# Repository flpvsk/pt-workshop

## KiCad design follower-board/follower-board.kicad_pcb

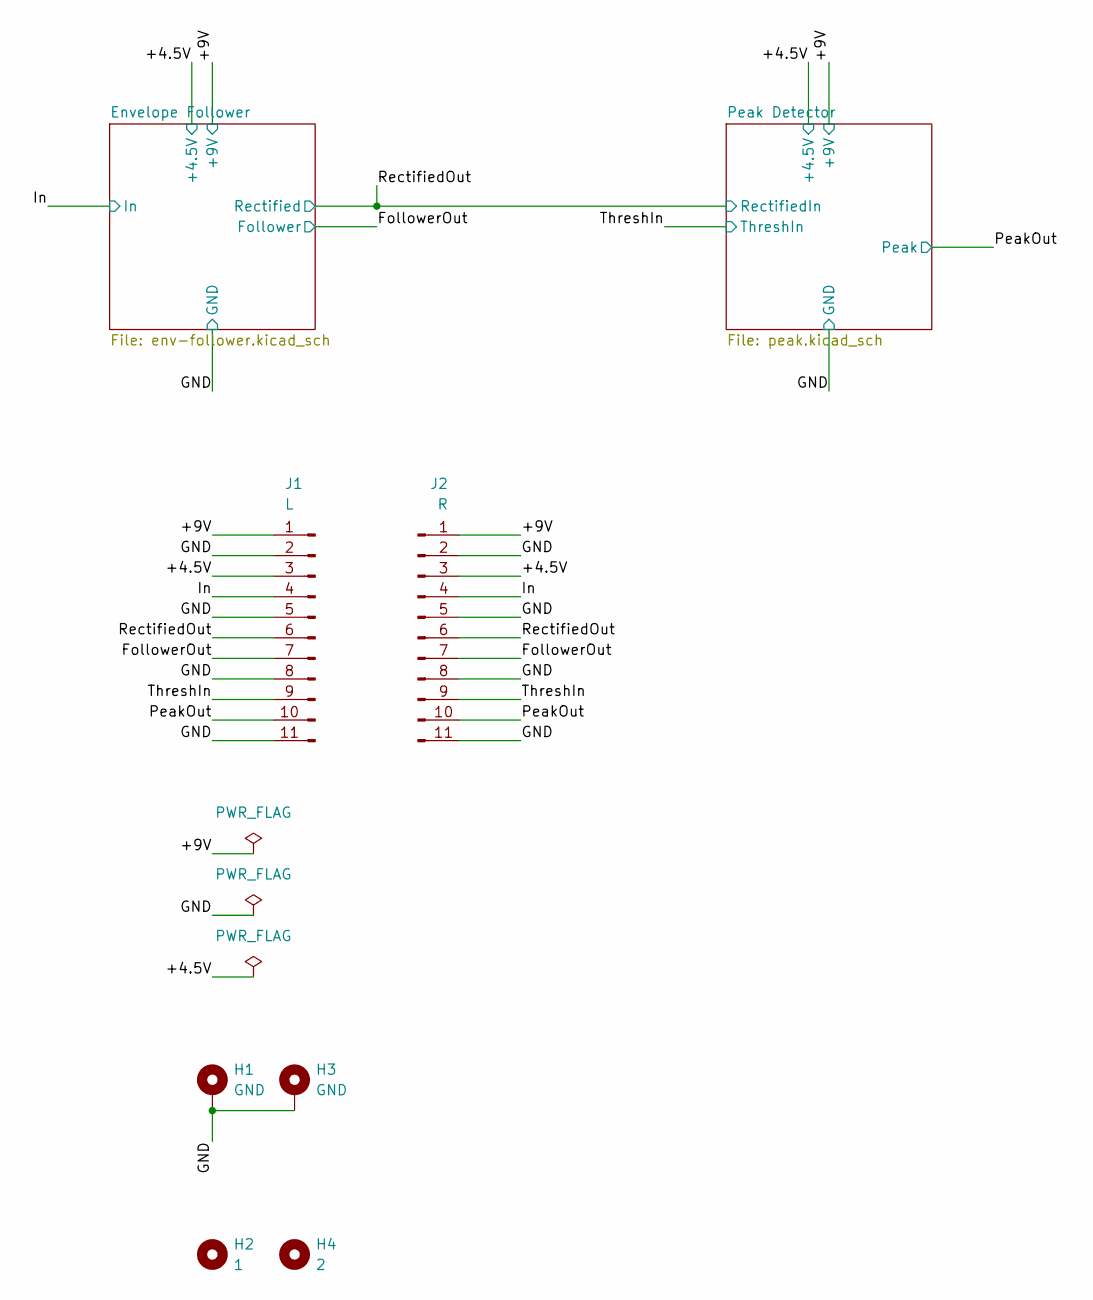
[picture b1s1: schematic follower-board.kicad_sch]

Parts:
H1, H3: GND; MountingHole_3.2mm_M3_ISO14580_Pad
H2: 1; MountingHole_3.2mm_M3
H4: 2; MountingHole_3.2mm_M3
J1: L; PinHeader_1x11_P2.54mm_Vertical
J2: R; PinHeader_1x11_P2.54mm_Vertical

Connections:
/+4.5V: J1.3, J2.3; also elsewhere on the board
/+9V: J1.1, J2.1; also elsewhere on the board
/FollowerOut: J1.7, J2.7; also elsewhere on the board
/GND: H1.1, H3.1, J1.2, J1.5, J1.8, J1.11, J2.2, J2.5, J2.8, J2.11; also elsewhere on the board
/In: J1.4, J2.4; also elsewhere on the board
/PeakOut: J1.10, J2.10; also elsewhere on the board
/RectifiedOut: J1.6, J2.6; also elsewhere on the board
/ThreshIn: J1.9, J2.9; also elsewhere on the board

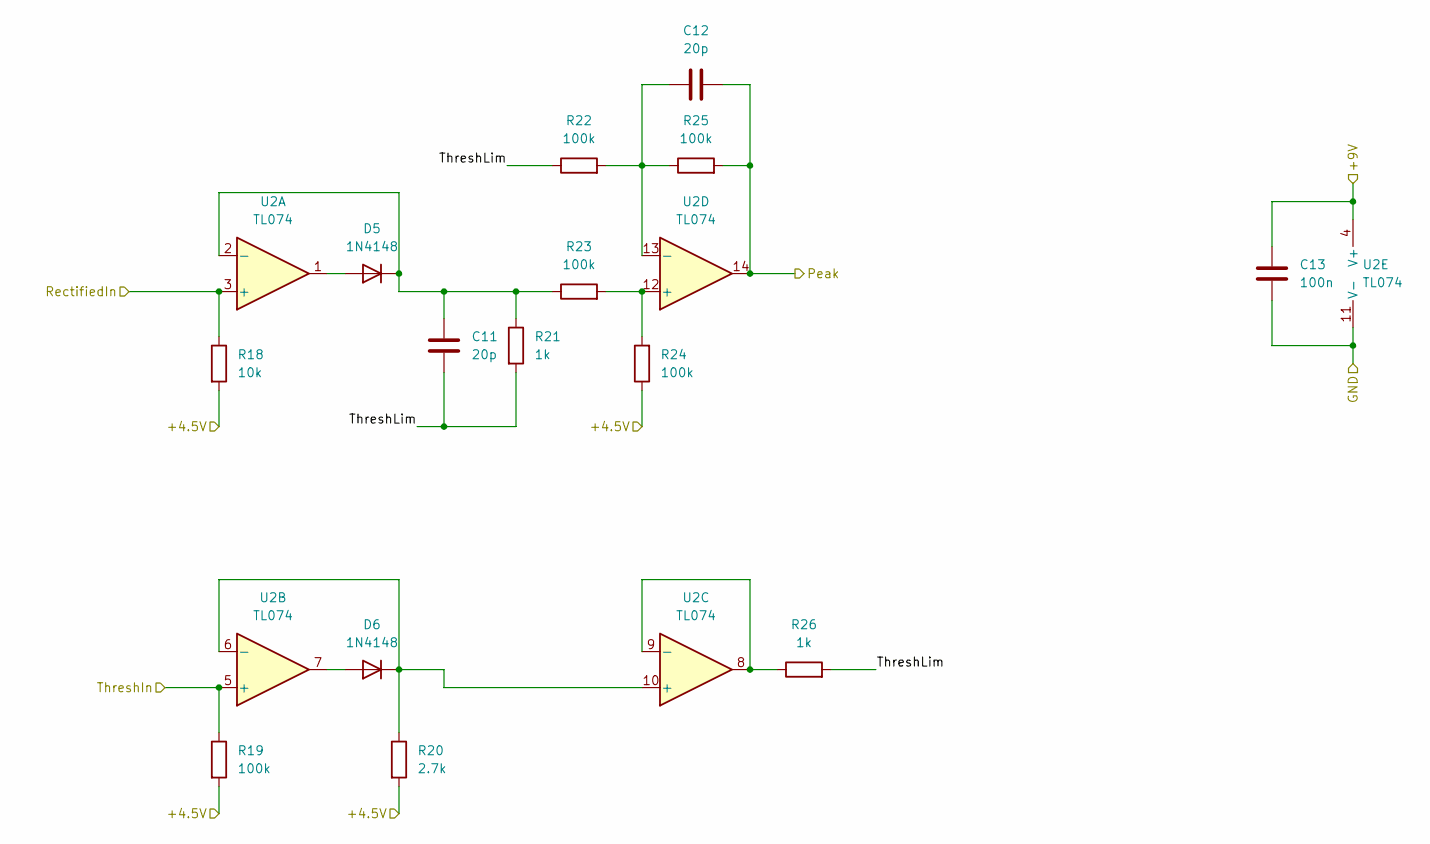
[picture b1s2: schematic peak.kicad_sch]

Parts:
C11, C12: 20p; C_0603_1608Metric_Pad1.08x0.95mm_HandSolder; LCSC C376774
C13: 100n; C_0603_1608Metric_Pad1.08x0.95mm_HandSolder; LCSC C76711
D5, D6: 1N4148; D_SOD-123; LCSC C81598
R18: 10k; R_0603_1608Metric_Pad0.98x0.95mm_HandSolder; LCSC C25804
R19, R22, R23, R24, R25: 100k; R_0603_1608Metric_Pad0.98x0.95mm_HandSolder; LCSC C25803
R20: 2.7k; R_0603_1608Metric_Pad0.98x0.95mm_HandSolder; LCSC C13167
R21, R26: 1k; R_0603_1608Metric_Pad0.98x0.95mm_HandSolder; LCSC C21190
U2: TL074; SOIC-14_3.9x8.7mm_P1.27mm; LCSC C6963

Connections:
/+4.5V: R18.2, R19.2, R20.2, R24.1; also elsewhere on the board
/+9V: C13.1, U2.4 (V+); also elsewhere on the board
/GND: C13.2, U2.11 (V-); also elsewhere on the board
/Peak Detector/ThreshLim: C11.2, R21.2, R22.1, R26.2
/PeakOut: C12.2, R25.2, U2.14; also elsewhere on the board
/RectifiedOut: R18.1, U2.3 (+); also elsewhere on the board
/ThreshIn: R19.1, U2.5 (+); also elsewhere on the board
unnamed: C11.1, D5.1 (K), R21.1, R23.1, U2.2 (-)
unnamed: C12.1, R22.2, R25.1, U2.13 (-)
unnamed: D5.2 (A), U2.1
unnamed: D6.1 (K), R20.1, U2.6 (-), U2.10 (+)
unnamed: D6.2 (A), U2.7
unnamed: R23.2, R24.2, U2.12 (+)
unnamed: R26.1, U2.8, U2.9 (-)

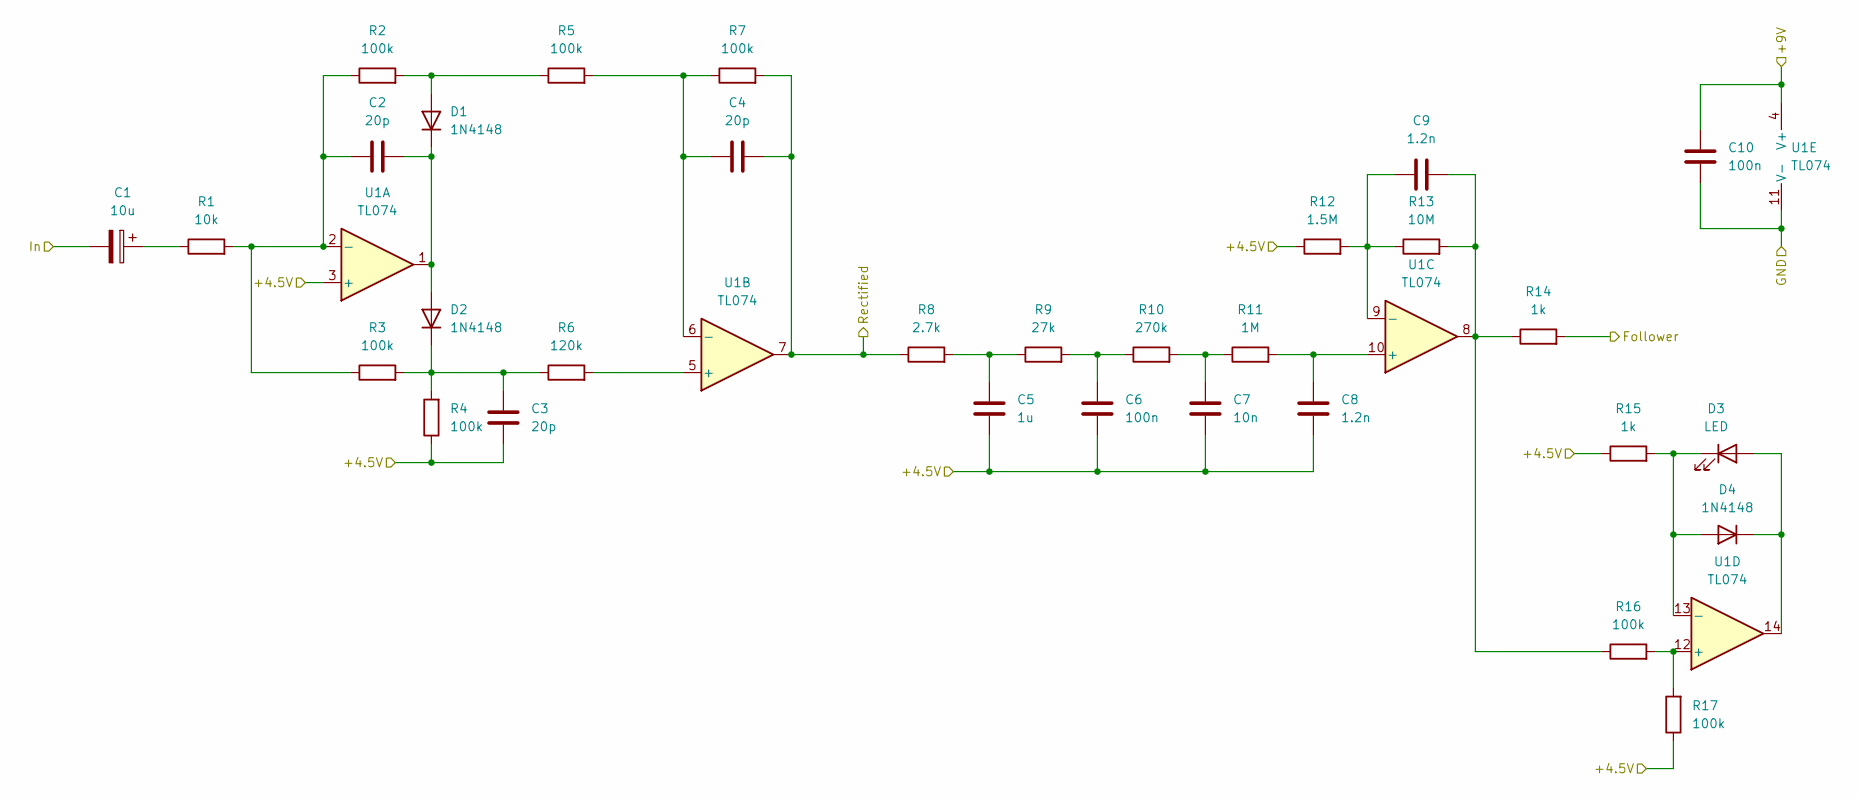
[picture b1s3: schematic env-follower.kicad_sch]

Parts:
C1: 10u; CP_Elec_5x5.4; LCSC C72486
C2, C3, C4: 20p; C_0603_1608Metric_Pad1.08x0.95mm_HandSolder; LCSC C376774
C5: 1u; C_0603_1608Metric_Pad1.08x0.95mm_HandSolder; LCSC C59302
C6, C10: 100n; C_0603_1608Metric_Pad1.08x0.95mm_HandSolder; LCSC C76711
C7: 10n; C_0603_1608Metric_Pad1.08x0.95mm_HandSolder; LCSC C1589
C8, C9: 1.2n; C_0603_1608Metric_Pad1.08x0.95mm_HandSolder; LCSC C107073
D1, D2, D4: 1N4148; D_SOD-123; LCSC C81598
D3: LED; LED_D3.0mm
R1: 10k; R_0603_1608Metric_Pad0.98x0.95mm_HandSolder; LCSC C25804
R2, R3, R4, R5, R7, R16, R17: 100k; R_0603_1608Metric_Pad0.98x0.95mm_HandSolder; LCSC C25803
R6: 120k; R_0603_1608Metric_Pad0.98x0.95mm_HandSolder; LCSC C25808
R8: 2.7k; R_0603_1608Metric_Pad0.98x0.95mm_HandSolder; LCSC C13167
R9: 27k; R_0603_1608Metric_Pad0.98x0.95mm_HandSolder; LCSC C22967
R10: 270k; R_0603_1608Metric_Pad0.98x0.95mm_HandSolder; LCSC C103491
R11: 1M; R_0603_1608Metric_Pad0.98x0.95mm_HandSolder; LCSC C2759765
R12: 1.5M; R_0603_1608Metric_Pad0.98x0.95mm_HandSolder; LCSC C445866
R13: 10M; R_0603_1608Metric_Pad0.98x0.95mm_HandSolder; LCSC C203213
R14, R15: 1k; R_0603_1608Metric_Pad0.98x0.95mm_HandSolder; LCSC C21190
U1: TL074; SOIC-14_3.9x8.7mm_P1.27mm; LCSC C6963

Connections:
/+4.5V: C3.1, C5.1, C6.1, C7.1, C8.1, R4.1, R12.1, R15.1, R17.1, U1.3 (+); also elsewhere on the board
/+9V: C10.1, U1.4 (V+); also elsewhere on the board
/FollowerOut: R14.2; also elsewhere on the board
/GND: C10.2, U1.11 (V-); also elsewhere on the board
/In: C1.2; also elsewhere on the board
/RectifiedOut: C4.2, R7.2, R8.1, U1.7; also elsewhere on the board
unnamed: C1.1, R1.1
unnamed: C2.1, R1.2, R2.1, R3.1, U1.2 (-)
unnamed: C2.2, D1.1 (K), D2.2 (A), U1.1
unnamed: C3.2, D2.1 (K), R3.2, R4.2, R6.1
unnamed: C4.1, R5.2, R7.1, U1.6 (-)
unnamed: C5.2, R8.2, R9.1
unnamed: C6.2, R9.2, R10.1
unnamed: C7.2, R10.2, R11.1
unnamed: C8.2, R11.2, U1.10 (+)
unnamed: C9.1, R13.2, R14.1, R16.1, U1.8
unnamed: C9.2, R12.2, R13.1, U1.9 (-)
unnamed: D1.2 (A), R2.2, R5.1
unnamed: D3.1 (K), D4.2 (A), R15.2, U1.13 (-)
unnamed: D3.2 (A), D4.1 (K), U1.14
unnamed: R6.2, U1.5 (+)
unnamed: R16.2, R17.2, U1.12 (+)

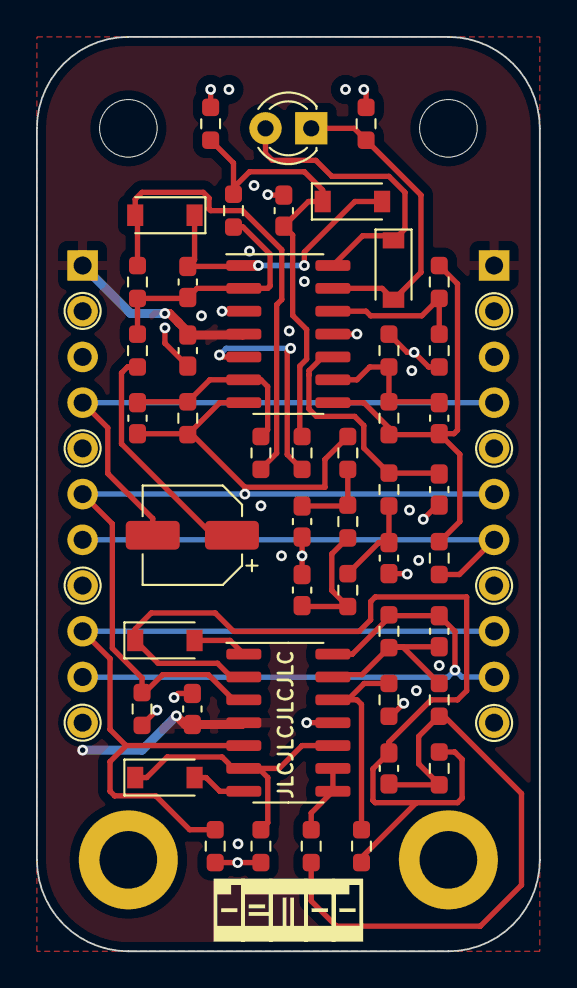
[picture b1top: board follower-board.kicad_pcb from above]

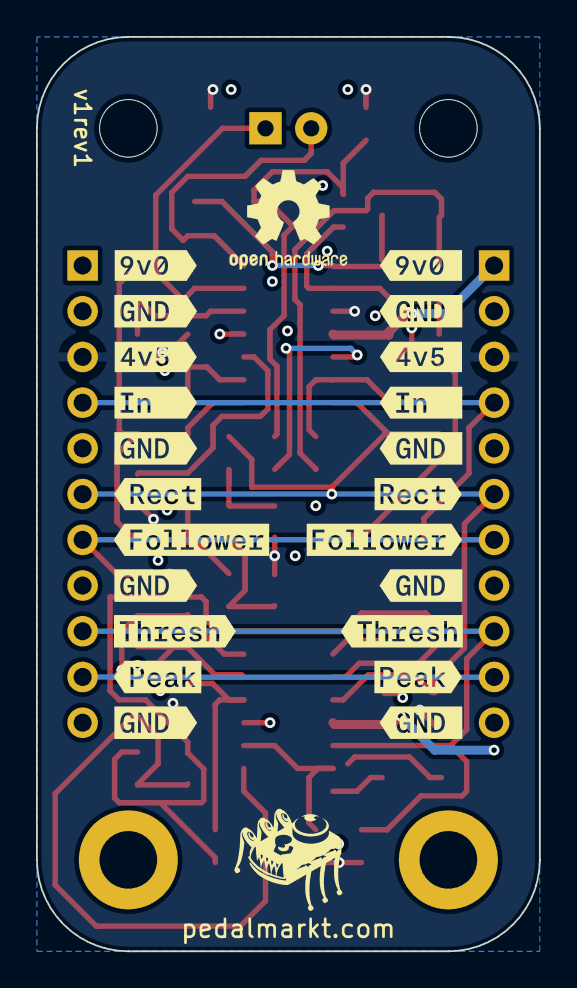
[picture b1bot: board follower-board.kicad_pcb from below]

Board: 4 copper layers, 27.9 x 50.8 mm, 76 parts (24 on the bottom side), 32 nets.

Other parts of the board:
kibuzzard-666B0D3F: G***; kibuzzard-666B0D3F
kibuzzard-666B0D4B, kibuzzard-666B0D4B#2, kibuzzard-666B0D4B#3, kibuzzard-666B0D4B#4: G***; kibuzzard-666B0D4B
kibuzzard-666B0D6E: G***; kibuzzard-666B0D6E
kibuzzard-666B0D54: G***; kibuzzard-666B0D54
kibuzzard-666B0D65: G***; kibuzzard-666B0D65
kibuzzard-666B0D69, kibuzzard-666B0D69#2, kibuzzard-666B0D69#3, kibuzzard-666B0D69#4: G***; kibuzzard-666B0D69
kibuzzard-6673DE4D: G***; kibuzzard-6673DE4D
kibuzzard-6673DFE6: G***; kibuzzard-6673DFE6
kibuzzard-6673E0D0: G***; kibuzzard-6673E0D0
kibuzzard-6673E1AC: G***; kibuzzard-6673E1AC
kibuzzard-6673E02E: G***; kibuzzard-6673E02E
kibuzzard-6673E072: G***; kibuzzard-6673E072
kibuzzard-6673E097: G***; kibuzzard-6673E097
kibuzzard-6673E113: G***; kibuzzard-6673E113
kibuzzard-6673E129: G***; kibuzzard-6673E129
kibuzzard-6673E139: G***; kibuzzard-6673E139
kibuzzard-6673E150: G***; kibuzzard-6673E150

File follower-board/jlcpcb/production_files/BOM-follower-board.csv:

Comment,Designator,Footprint,LCSC
270k,R10,R_0603_1608Metric_Pad0.98x0.95mm_HandSolder,C103491
1.2n,"C8,C9",C_0603_1608Metric_Pad1.08x0.95mm_HandSolder,C107073
2.7k,"R20,R8",R_0603_1608Metric_Pad0.98x0.95mm_HandSolder,C13167
10n,C7,C_0603_1608Metric_Pad1.08x0.95mm_HandSolder,C1589
10M,R13,R_0603_1608Metric_Pad0.98x0.95mm_HandSolder,C203213
1k,"R14,R15,R21,R26",R_0603_1608Metric_Pad0.98x0.95mm_HandSolder,C21190
27k,R9,R_0603_1608Metric_Pad0.98x0.95mm_HandSolder,C22967
100k,"R16,R17,R19,R2,R22,R23,R24,R25,R3,R4,R5,R7",R_0603_1608Metric_Pad0.98x0.95mm_HandSolder,C25803
10k,"R1,R18",R_0603_1608Metric_Pad0.98x0.95mm_HandSolder,C25804
120k,R6,R_0603_1608Metric_Pad0.98x0.95mm_HandSolder,C25808
1M,R11,R_0603_1608Metric_Pad0.98x0.95mm_HandSolder,C2759765
20p,"C11,C12,C2,C3,C4",C_0603_1608Metric_Pad1.08x0.95mm_HandSolder,C376774
1.5M,R12,R_0603_1608Metric_Pad0.98x0.95mm_HandSolder,C445866
1u,C5,C_0603_1608Metric_Pad1.08x0.95mm_HandSolder,C59302
TL074,"U1,U2",SOIC-14_3.9x8.7mm_P1.27mm,C6963
10u,C1,CP_Elec_5x5.4,C72486
100n,"C10,C13,C6",C_0603_1608Metric_Pad1.08x0.95mm_HandSolder,C76711
1N4148,"D1,D2,D4,D5,D6",D_SOD-123,C81598
1,H2,MountingHole_3.2mm_M3,
LED,D3,LED_D3.0mm,
GND,H3,MountingHole_3.2mm_M3_ISO14580_Pad,
GND,H1,MountingHole_3.2mm_M3_ISO14580_Pad,
2,H4,MountingHole_3.2mm_M3,
L,J1,PinHeader_1x11_P2.54mm_Vertical,
R,J2,PinHeader_1x11_P2.54mm_Vertical,
